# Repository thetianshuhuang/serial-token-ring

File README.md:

# Serial Ring Network

## Protocol
Clients should be connected via UART at 115200 baud in a ring topology. Packets should consist of at least 3 bytes:
```
| 0xAA | SRC | DST | SIZE | ---MSG--- | CHK |
```
### 0xAA
Mesage begin header; all packets must begin with 0xAA.

This is to minimize the impact of packets with misplaced SIZE values; if a previous packet dropped two bytes, without a message begin byte to check, the size byte would be interpreted as the source, and the first byte of the message would be interpreted as the SIZE value. If the message began with 0xFF or another large number, this could cause cascades of dropped packets.

### SRC
Source address. Each client should have a unique 8-bit source address obtained either from EEPROM or by some form of hardware. Using a voltage divider with varying resistor values is suggested.

### DST
Destination address. Packets should not be forwarded by their destination. 0x00 is reserved for peer discovery and broadcast.

### SIZE
Size of the message. Since SIZE is an 8-bit value, message sizes are limited to 255 bytes. Null messages are possible, and should be interpreted and forwarded as appropriate by the network driver.

### MSG
Message contents. Since a SIZE identifier is used to specify the message length, null characters are allowed in the message.

The first byte in peer discovery messages should be reserved for an application identifier.

### CHK
8-bit checksum. Computed as the XOR of all bytes in the message, except for the message initializer.

## Suggested implementation

Since this protocol is designed to operate on embedded systems, impelmentations should be platform-independent where possible. Two functions should be defined:

```
update:
	Read input buffer, and append to the function buffer
	If no message is in the input buffer, discard all bytes until 0xAA is recieved.
	Check to see if the message has been finished. If not, return a null string.
	Compute the checksum of the message; if it does not match the recieved checksum, discard the message
	Terminate the message if SRC or DST match the device address
	Forward the message if not terminated
	Return the recieved message if SRC[7] = 1 (broadcast) or DST matches the device address.
	Return a null string

send:
	Send 0xAA
	Begin keeping track of all sent bytes for the checksum
	Send SRC, DST, SIZE, MSG
	Send CHK
```

It is suggested that this module should be initialized with a send function and a recieve function as function pointers in order to maximize interoperability.

The user is responsible for calling update at least once every 500us either in a main loop, through a periodic interrupt, or through a UART buffer interrupt.

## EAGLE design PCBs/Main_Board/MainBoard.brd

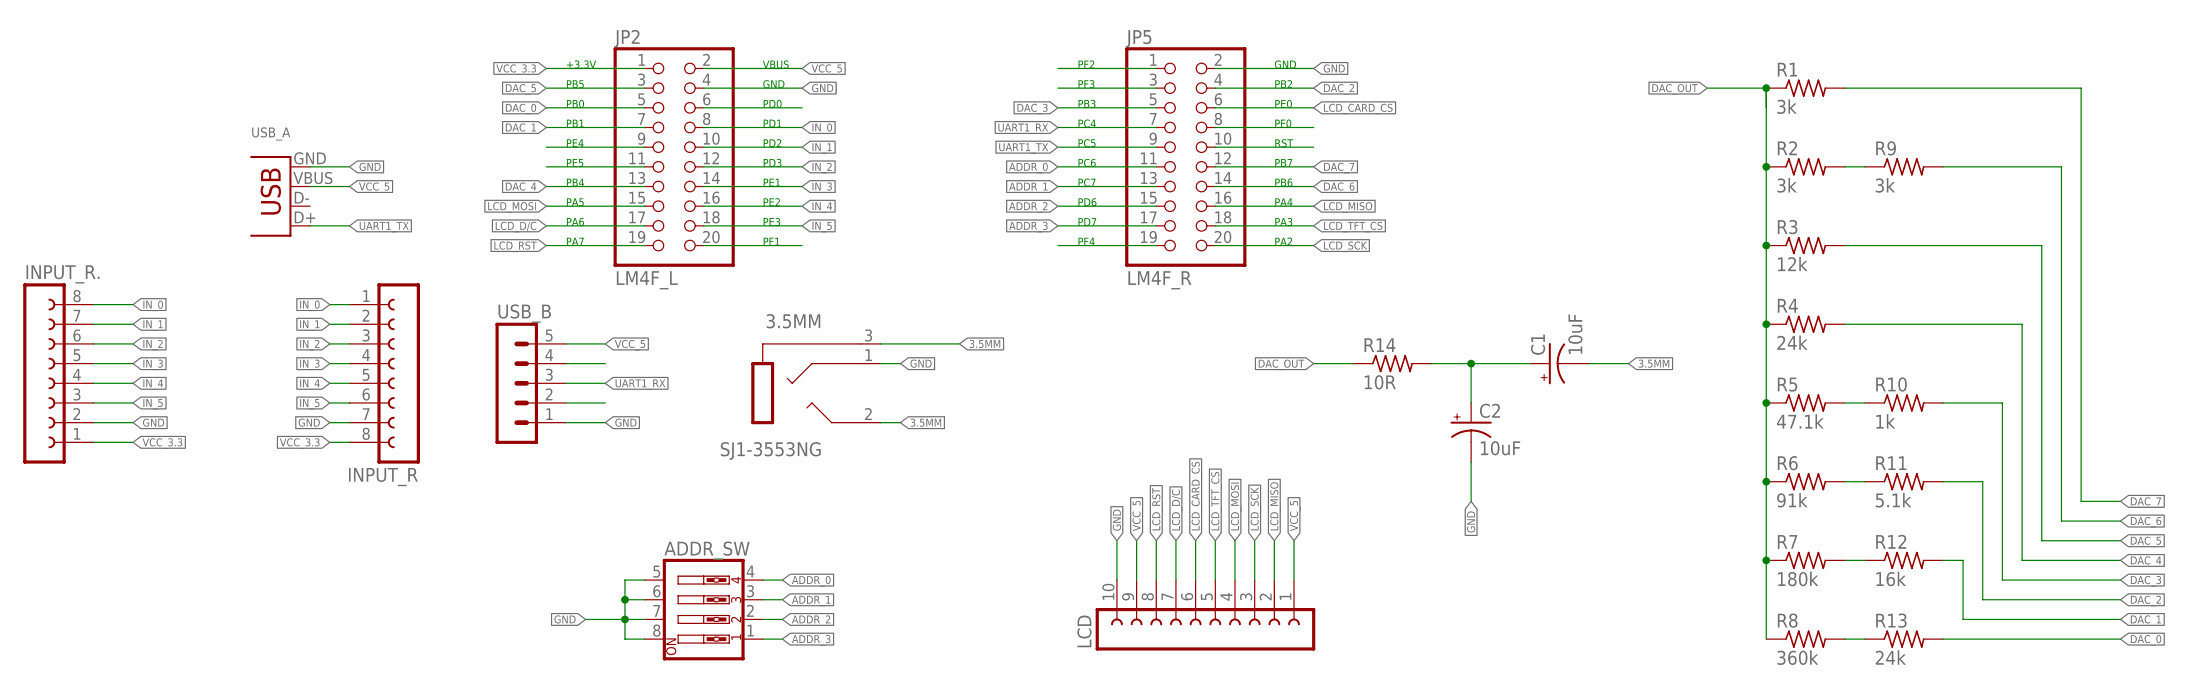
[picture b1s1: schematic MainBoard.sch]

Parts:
3.5MM: SJ1-3553NG
ADDR_SW: SW_DIP-4; EDG-04
C1, C2: 10uF; E2-4
INPUT_R, INPUT_R.: FE08W
JP2: LM4F_L; 2X10
JP5: LM4F_R; 2X10
LCD: FE10-1; FE10
R1, R2, R9: 3k; 0309/10
R3: 12k; 0309/10
R4, R13: 24k; 0309/10
R5: 47.1k; 0309/10
R6: 91k; 0309/10
R7: 180k; 0309/10
R8: 360k; 0309/10
R10: 1k; 0309/10
R11: 5.1k; 0309/10
R12: 16k; 0309/10
R14: 10R; 0309/10
USB_A: USB-A-H
USB_B: MA05-1

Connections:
3.5MM: 3.5MM.2 (TIP), 3.5MM.3 (SLEEVE), C1.-
ADDR_0: ADDR_SW.4, JP5.11
ADDR_1: ADDR_SW.3, JP5.13
ADDR_2: ADDR_SW.2, JP5.15
ADDR_3: ADDR_SW.1, JP5.17
DAC_0: JP2.5, R13.2
DAC_1: JP2.7, R12.2
DAC_2: JP5.4, R11.2
DAC_3: JP5.5, R10.2
DAC_4: JP2.13, R4.2
DAC_5: JP2.3, R3.2
DAC_6: JP5.14, R9.2
DAC_7: JP5.12, R1.2
DAC_OUT: R1.1, R2.1, R3.1, R4.1, R5.1, R6.1, R7.1, R8.1, R14.1
GND: 3.5MM.1 (RING), ADDR_SW.5, ADDR_SW.6, ADDR_SW.7, ADDR_SW.8, C2.-, INPUT_R.7, INPUT_R..2, JP2.4, JP5.2, LCD.10, USB_A.GND, USB_B.1
IN_0: INPUT_R.1, INPUT_R..8, JP2.8
IN_1: INPUT_R.2, INPUT_R..7, JP2.10
IN_2: INPUT_R.3, INPUT_R..6, JP2.12
IN_3: INPUT_R.4, INPUT_R..5, JP2.14
IN_4: INPUT_R.5, INPUT_R..4, JP2.16
IN_5: INPUT_R.6, INPUT_R..3, JP2.18
LCD_CARD_CS: JP5.6, LCD.6
LCD_D/C: JP2.17, LCD.7
LCD_MISO: JP5.16, LCD.2
LCD_MOSI: JP2.15, LCD.4
LCD_RST: JP2.19, LCD.8
LCD_SCK: JP5.20, LCD.3
LCD_TFT_CS: JP5.18, LCD.5
unnamed: C1.+, C2.+, R14.2
unnamed: R7.2, R12.1
unnamed: R8.2, R13.1
unnamed: R2.2, R9.1
unnamed: R5.2, R10.1
unnamed: R6.2, R11.1
PD0: JP2.6
PE4: JP2.9
PE5: JP2.11
PF0: JP5.8
PF1: JP2.20
PF2: JP5.1
PF3: JP5.3
PF4: JP5.19
RST: JP5.10
UART1_RX: JP5.7, USB_B.3
UART1_TX: JP5.9, USB_A.D+
VCC_3.3: INPUT_R.8, INPUT_R..1, JP2.1
VCC_5: JP2.2, LCD.1, LCD.9, USB_A.VBUS, USB_B.5

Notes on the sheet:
+3.3V
PB5
PB0
PB1
PE4
PE5
PB4
PA5
PA6
PA7
VBUS
GND
PD0
PD1
PD2
PD3
PE1
PE2
PE3
PF1
PF2
PF3
PB3
PC4
PC5
PC6
PC7
PF4
PB2
PE0
PF0
RST
PB7
PB6
PA4
PA3
PA2
PD6
PD7

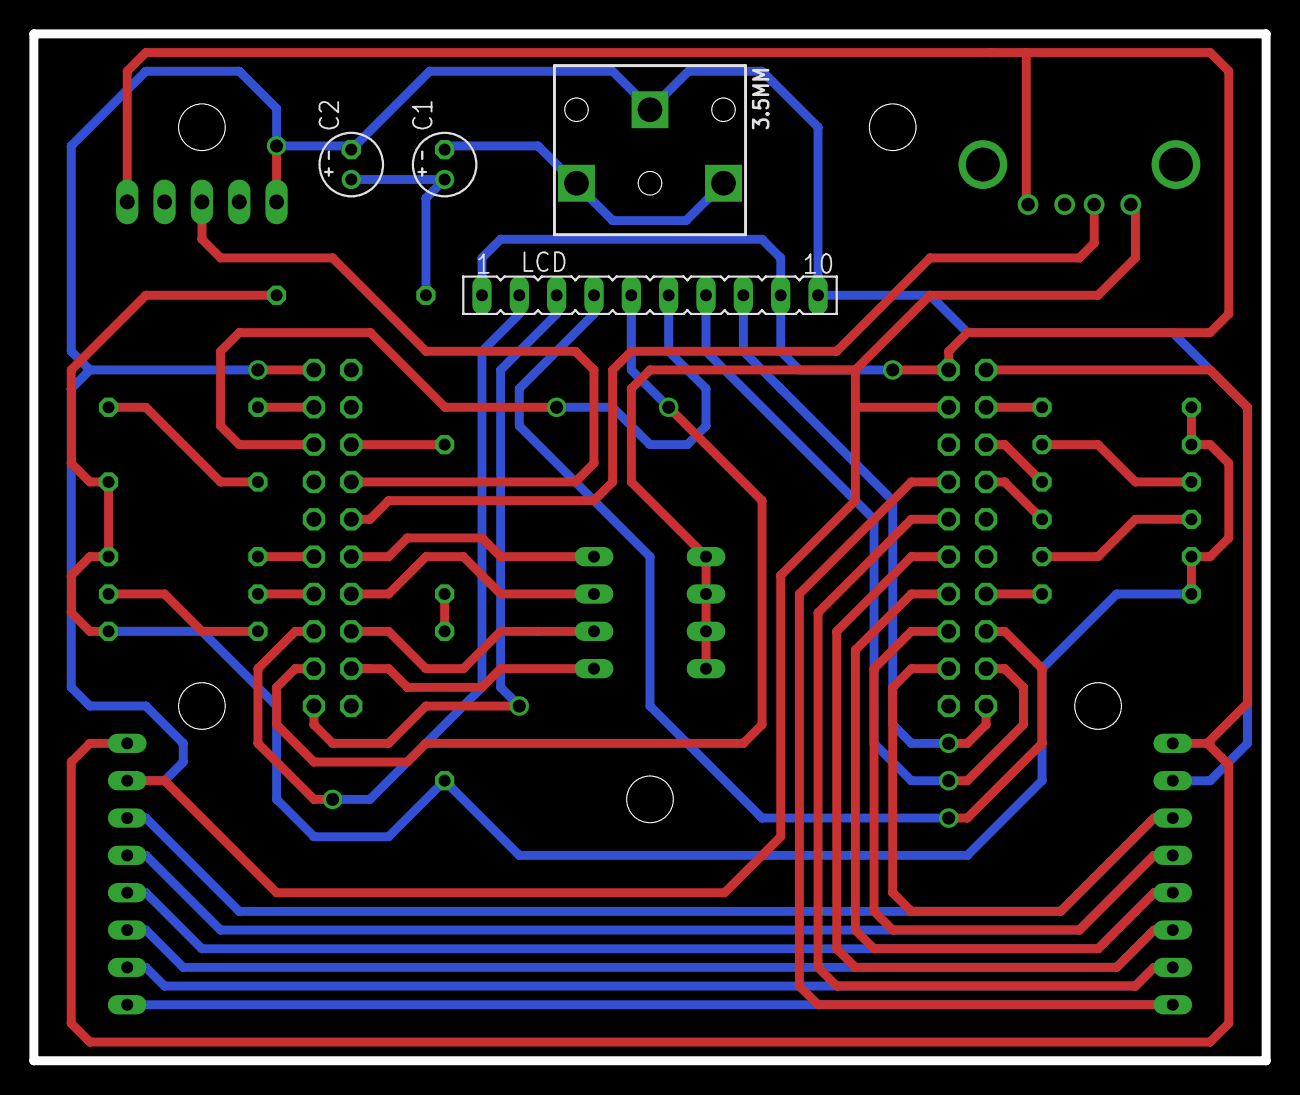
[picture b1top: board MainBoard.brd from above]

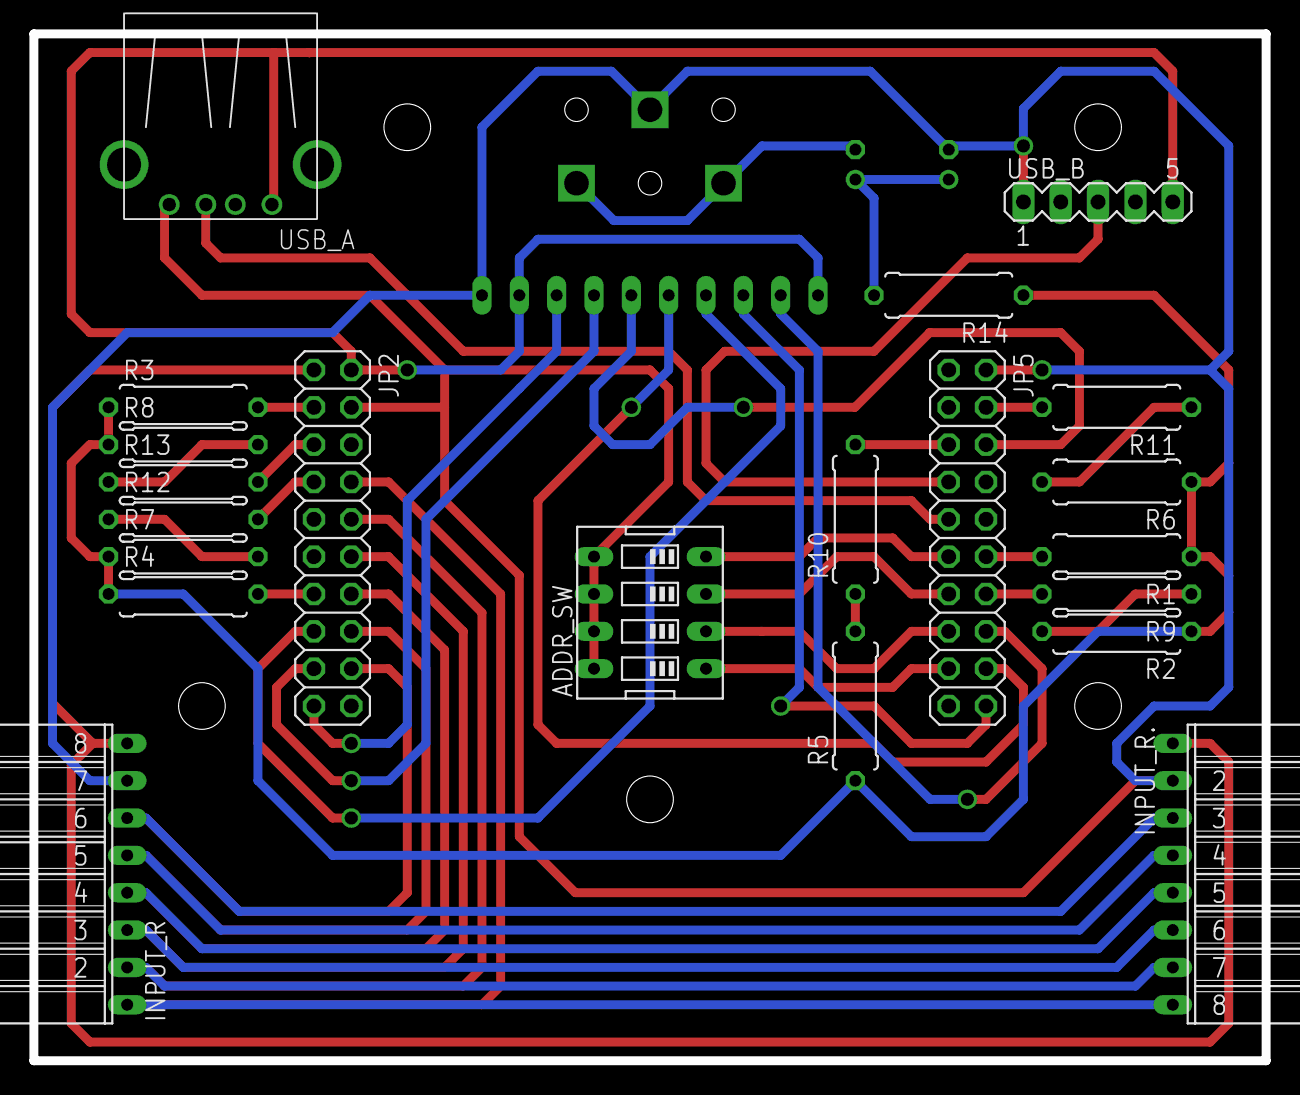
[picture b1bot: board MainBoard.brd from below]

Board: 2 copper layers, 83.8 x 69.8 mm, 25 parts (21 on the bottom side), 38 nets.

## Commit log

2018-03-28 Finished protocol description
2018-03-28 Started on python client
2018-03-28 Added 'starter code' for C framework
2018-03-28 Changed peer discovery to reserved address (as per @benbelov's recommendation)
2018-03-28 Made DST mandatory
2018-03-28 Added bare c client
2018-03-28 Added C++ client framework
2018-03-28 Wrote C++ client
2018-03-28 Started on arduino driver
2018-03-28 Added example arduino impelmentation
2018-03-28 Set up TM4C folder, gitignore for Keil
2018-03-28 Added TM4C implementation (untested)
2018-04-19 Removed references to token rings
2018-04-19 Added mainboard pcb file FROM HELL
2018-04-19 Added DIP switch and fixed USB
2018-04-19 Minor changes to main board
2018-04-20 Created main board layout
2018-04-20 Swapped D+/D- pins on the USB A port; misc optimizations
2018-04-20 Undid swap
2018-04-20 Enlarged holes to only require 1/32 and 80 degree engraving bit
2018-04-20 Widened traces
2018-04-28 Cleaned up client code
2018-05-01 Fixed include typo
2018-05-01 Datatype and function passing bug fixes
2018-05-03 Added interrupt-style implementation
